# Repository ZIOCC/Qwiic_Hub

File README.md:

# Qwiic_Hub

> This product can be available for purchase [here](https://www.smart-prototyping.com/Zio-Qwiic-Hub.html).

#### Description

Want to split your Qwiic [bus](https://en.wikipedia.org/wiki/Bus_network) into a [tree](https://en.wikipedia.org/wiki/Tree_network)? Grab a hub! 

The Zio Qwiic Hub is a simple board with 4 Qwiic connectors in parallel. Just connect your main Qwiic bus to one of those ports, and split it into as many as three chains of modules.

Building a humanoid robotic torso and want to put a servo controller on each arm without creating unnecessary capacitance by running your bus down one arm and back to get to the other? Perfect! Just use the hub to split your bus, and you’re good to go.

The board is easily mountable due to the inclusion of a 3mm mounting hole.

#### Specification

* 4 Qwiic Connectors
* Weight: 5g
* Dimension: 30.1x12.0 mm

#### Links

* [Eagle files](https://github.com/ZIOCC/Qwiic_Hub)

> ###### About Zio
> Zio is a new line of open sourced, compact, and grid layout boards, fully integrated for Arduino and Qwiic ecosystem. Designed ideally for wearables, robotics, small-space limitations or other on the go projects. Check out other awesome Zio products [here](https://www.smart-prototyping.com/Zio).

> All Zio products are released under the [Creative Commons Attribution, Share-Alike License](https://creativecommons.org/licenses/by-sa/4.0/), and in accordance with the principles of the [Open Source Hardware Association's OSHW Statement of Principles 1.0 and OSHW Definition 1.0](https://www.oshwa.org/definition/).

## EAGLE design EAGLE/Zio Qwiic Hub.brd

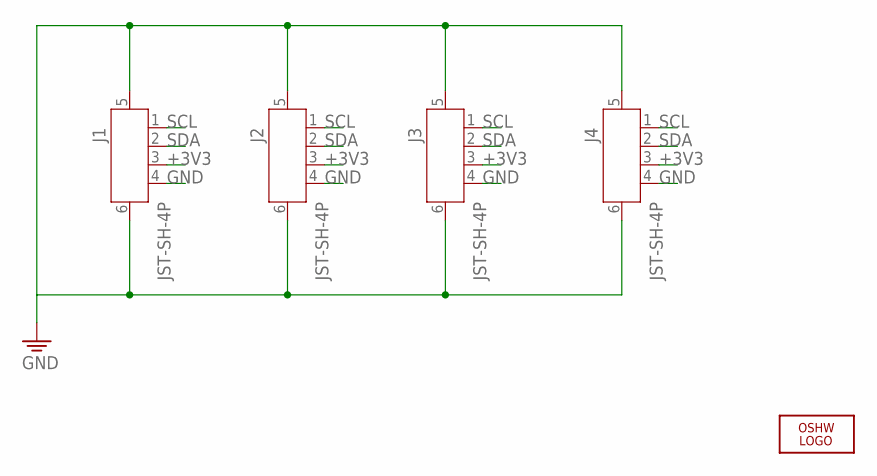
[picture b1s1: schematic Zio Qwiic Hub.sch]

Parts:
J1, J2, J3, J4: JST-SH-4P; JST-SH-4P-90
LOGO1: LOGO-OSHW-6MILX0070-NT; OSHW_6X70_NOTEXT

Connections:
+3V3: J1.3, J2.3, J3.3, J4.3
GND: J1.4, J1.5, J1.6, J2.4, J2.5, J2.6, J3.4, J3.5, J3.6, J4.4, J4.5, J4.6
SCL: J1.1, J2.1, J3.1, J4.1
SDA: J1.2, J2.2, J3.2, J4.2

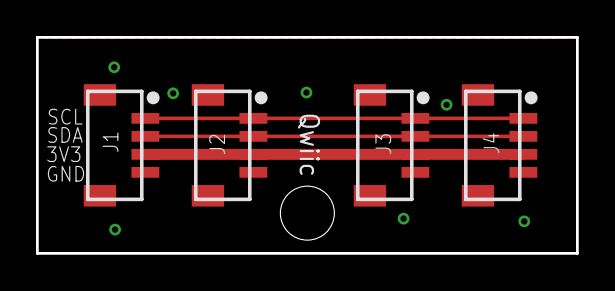
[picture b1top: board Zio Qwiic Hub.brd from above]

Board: 2 copper layers, 30.0 x 12.0 mm, 6 parts (2 on the bottom side), 4 nets.

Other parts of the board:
E$10: 7MM
